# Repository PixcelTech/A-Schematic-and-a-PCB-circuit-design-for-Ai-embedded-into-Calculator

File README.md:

# A-Schematic-and-a-PCB-circuit-design-for-Ai-embedded-into-Calculator
A Schematic and a PCB circuit design for Ai embedded into Calculator

if you want it run it fine in your Kicad then download all the files in
the main branch and place them in a folder and then opened then opened that 
folder through Kicad.

CON 
it is a wifi connected and it has a small light then tell you if the wifi is working

light = blinking (wifi not working)

light = stable (wifi fine)

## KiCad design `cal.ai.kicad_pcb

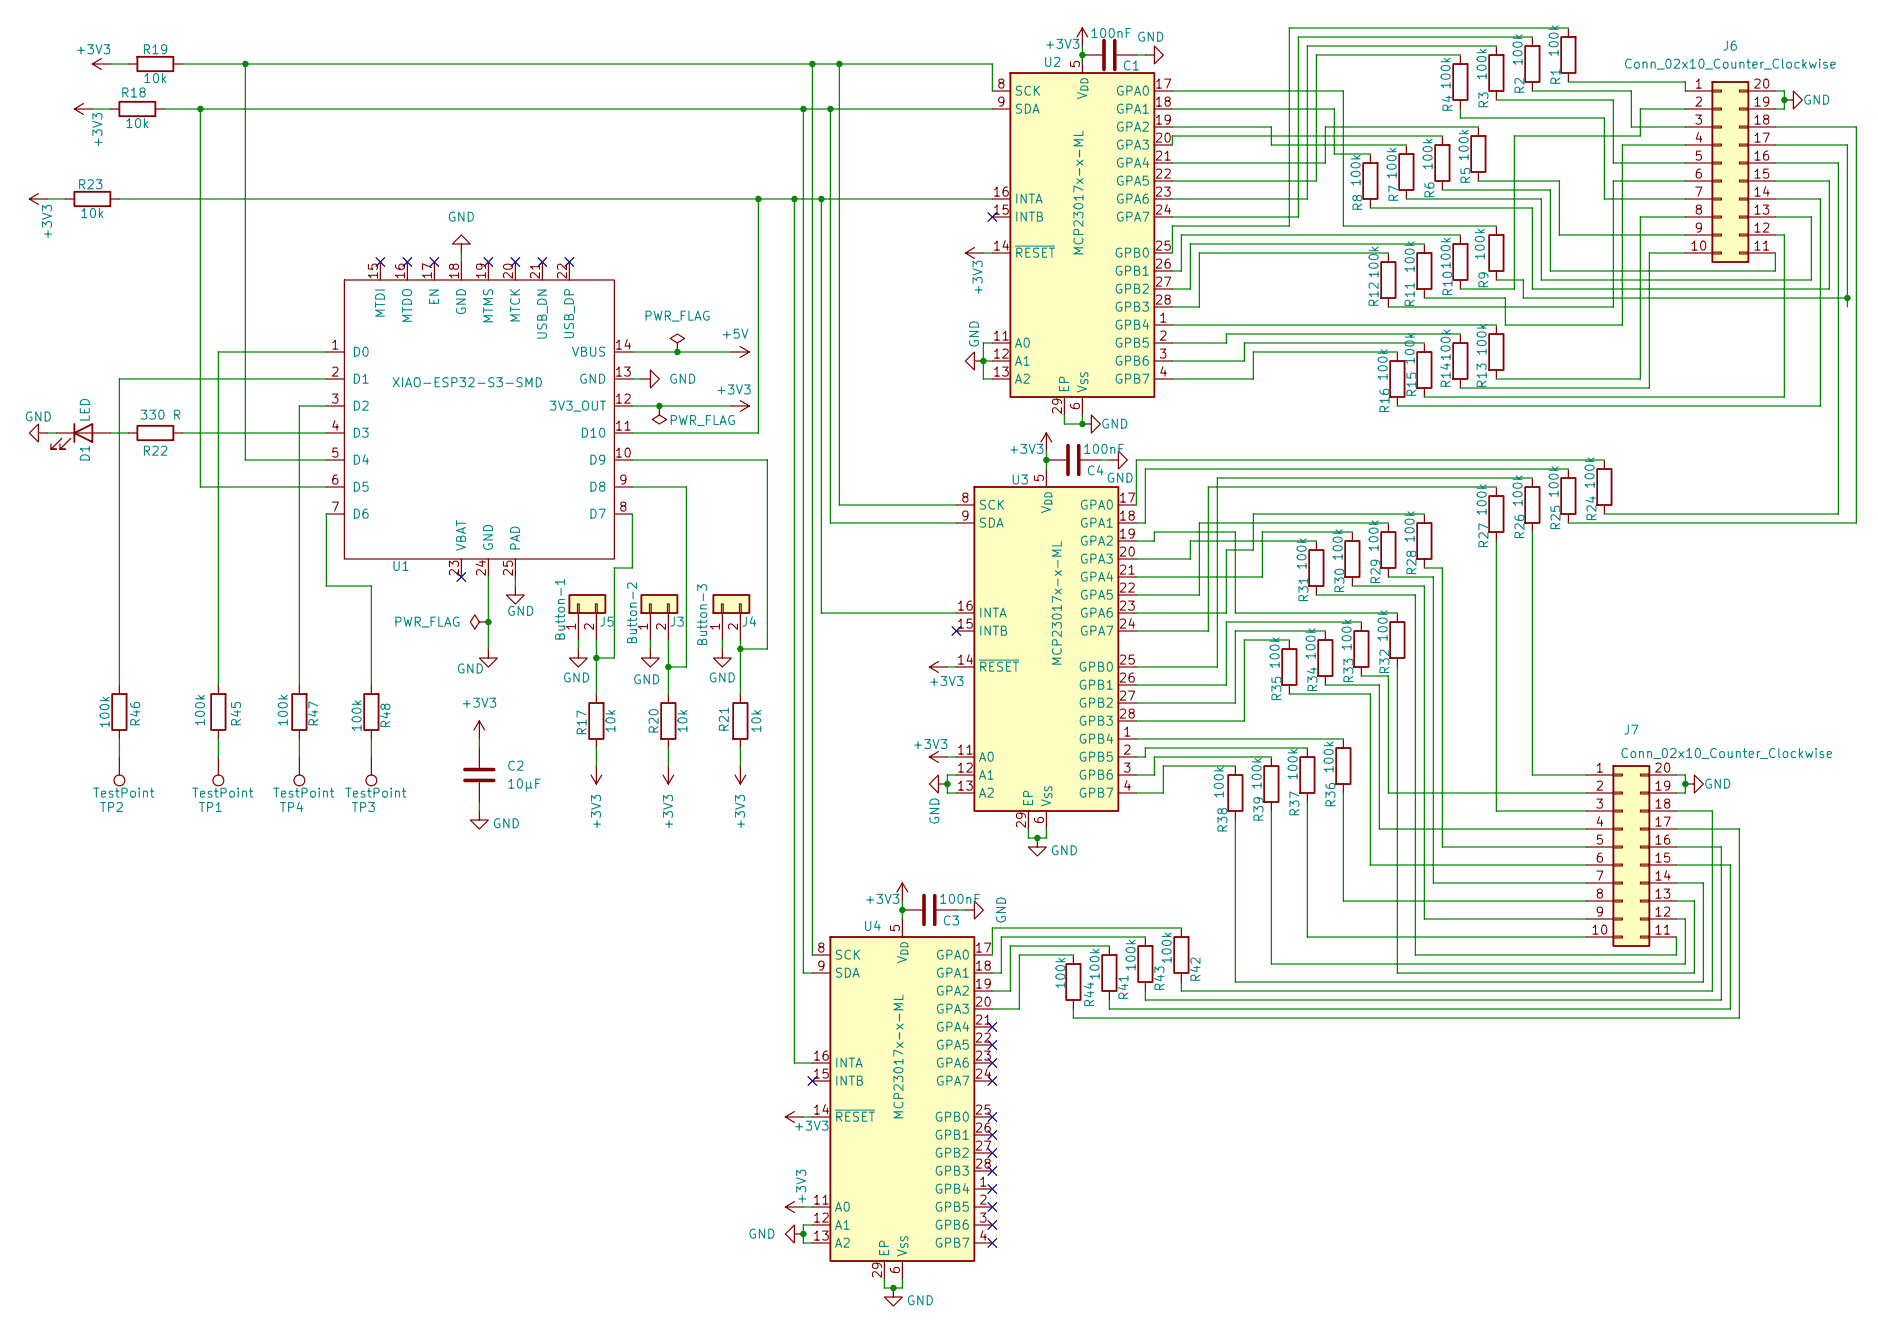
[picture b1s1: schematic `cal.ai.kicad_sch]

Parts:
C1, C3, C4: 100nF; C_0603_1608Metric
C2: 10µF; C_0805_2012Metric
D1: LED; LED_0402_1005Metric
J3: Button-2; PinHeader_1x02_P2.54mm_Vertical
J4: Button-3; PinHeader_1x02_P2.54mm_Vertical
J5: Button-1; PinHeader_1x02_P2.54mm_Vertical
J6, J7: Conn_02x10_Counter_Clockwise; PinHeader_2x10_P2.54mm_Vertical
R1, R2, R3, R4, R5, R6, R7, R8, R9, R10, R11, R12, R13, R14, R15, R16, R24, R25, R26, R27, R28, R29, R30, R31, R32, R33, R34, R35, R36, R37, R38, R39, R41, R42, R43, R44, R45, R46, R47, R48: 100k; R_0603_1608Metric
R17, R18, R19, R20, R21, R23: 10k; R_0603_1608Metric
R22: 330 R; R_0603_1608Metric
TP1, TP2, TP3, TP4: TestPoint; TestPoint_Loop_D1.80mm_Drill1.0mm_Beaded
U1: XIAO-ESP32-S3-SMD
U2, U3, U4: MCP23017x-x-ML; QFN-28-1EP_6x6mm_P0.65mm_EP4.25x4.25mm

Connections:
+3V3: C1.2, C2.1, C3.2, C4.2, R17.1, R18.1, R19.2, R20.2, R21.2, R23.1, U1.12 (3V3_OUT), U2.5 (V_{DD}), U2.14 (~RESET), U3.5 (V_{DD}), U3.11 (A0), U3.14 (~RESET), U4.5 (V_{DD}), U4.11 (A0), U4.14 (~RESET)
+5V: U1.14 (VBUS)
GND: C1.1, C2.2, C3.1, C4.1, D1.1 (K), J3.1, J4.1, J5.1, J6.19, J6.20, J7.19, J7.20, U1.13 (GND), U1.18 (GND), U1.24 (GND), U1.25 (PAD), U2.6 (V_{SS}), U2.11 (A0), U2.12 (A1), U2.13 (A2), U2.29 (EP), U3.6 (V_{SS}), U3.12 (A1), U3.13 (A2), U3.29 (EP), U4.6 (V_{SS}), U4.12 (A1), U4.13 (A2), U4.29 (EP)
unnamed: D1.2 (A), R22.1
unnamed: J3.2, R20.1, U1.9 (D8)
unnamed: J4.2, R21.1, U1.10 (D9)
unnamed: J5.2, R17.2, U1.8 (D7)
unnamed: J6.1, R1.1
unnamed: J6.2, R10.1
unnamed: J6.3, R2.1
unnamed: J6.4, R11.2
unnamed: J6.5, R3.1
unnamed: J6.6, R12.2
unnamed: J6.7, R4.1
unnamed: J6.8, R13.2
unnamed: J6.9, R5.1
unnamed: J6.10, R14.2
unnamed: J6.11, R6.1
unnamed: J6.12, R15.2
unnamed: J6.13, R7.1
unnamed: J6.14, R16.2
unnamed: J6.15, R8.1
unnamed: J6.16, R24.2
unnamed: J6.17, R9.1
unnamed: J6.18, R25.2
unnamed: J7.1, R26.2
unnamed: J7.2, R33.2
unnamed: J7.3, R27.2
unnamed: J7.4, R34.2
unnamed: J7.5, R28.2
unnamed: J7.6, R35.2
unnamed: J7.7, R29.2
unnamed: J7.8, R36.2
unnamed: J7.9, R30.2
unnamed: J7.10, R37.2
unnamed: J7.11, R31.2
unnamed: J7.12, R39.2
unnamed: J7.13, R32.2
unnamed: J7.14, R38.2
unnamed: J7.15, R41.1
unnamed: J7.16, R43.1
unnamed: J7.17, R44.1
unnamed: J7.18, R42.1
unnamed: R45.1, TP1.1 (1_1)
unnamed: R46.1, TP2.1 (1_1)
unnamed: R47.1, TP4.1 (1_1)
unnamed: R48.1, TP3.1 (1_1)
unnamed: R45.2, U1.1 (D0)
unnamed: R46.2, U1.2 (D1)
unnamed: R47.2, U1.3 (D2)
unnamed: R22.2, U1.4 (D3)
unnamed: R19.1, U1.5 (D4), U2.8 (SCK), U3.8 (SCK), U4.8 (SCK)
unnamed: R18.2, U1.6 (D5), U2.9 (SDA), U3.9 (SDA), U4.9 (SDA)
unnamed: R48.2, U1.7 (D6)
unnamed: R23.2, U1.11 (D10), U2.16 (INTA), U3.16 (INTA), U4.16 (INTA)
unnamed: R9.2, U2.17 (GPA0)
unnamed: R8.2, U2.18 (GPA1)
unnamed: R7.2, U2.19 (GPA2)
unnamed: R6.2, U2.20 (GPA3)
unnamed: R5.2, U2.21 (GPA4)
unnamed: R4.2, U2.22 (GPA5)
unnamed: R3.2, U2.23 (GPA6)
unnamed: R2.2, U2.24 (GPA7)
unnamed: R1.2, U2.25 (GPB0)
unnamed: R10.2, U2.26 (GPB1)
unnamed: R11.1, U2.27 (GPB2)
unnamed: R12.1, U2.28 (GPB3)
unnamed: R13.1, U2.1 (GPB4)
unnamed: R14.1, U2.2 (GPB5)
unnamed: R15.1, U2.3 (GPB6)
unnamed: R16.1, U2.4 (GPB7)
unnamed: R24.1, U3.17 (GPA0)
unnamed: R25.1, U3.18 (GPA1)
unnamed: R32.1, U3.19 (GPA2)
unnamed: R31.1, U3.20 (GPA3)
unnamed: R30.1, U3.21 (GPA4)
unnamed: R29.1, U3.22 (GPA5)
unnamed: R28.1, U3.23 (GPA6)
unnamed: R27.1, U3.24 (GPA7)
unnamed: R26.1, U3.25 (GPB0)
unnamed: R33.1, U3.26 (GPB1)
unnamed: R34.1, U3.27 (GPB2)
unnamed: R35.1, U3.28 (GPB3)
unnamed: R36.1, U3.1 (GPB4)
unnamed: R37.1, U3.2 (GPB5)
unnamed: R39.1, U3.3 (GPB6)
unnamed: R38.1, U3.4 (GPB7)
unnamed: R42.2, U4.17 (GPA0)
unnamed: R43.2, U4.18 (GPA1)
unnamed: R41.2, U4.19 (GPA2)
unnamed: R44.2, U4.20 (GPA3)

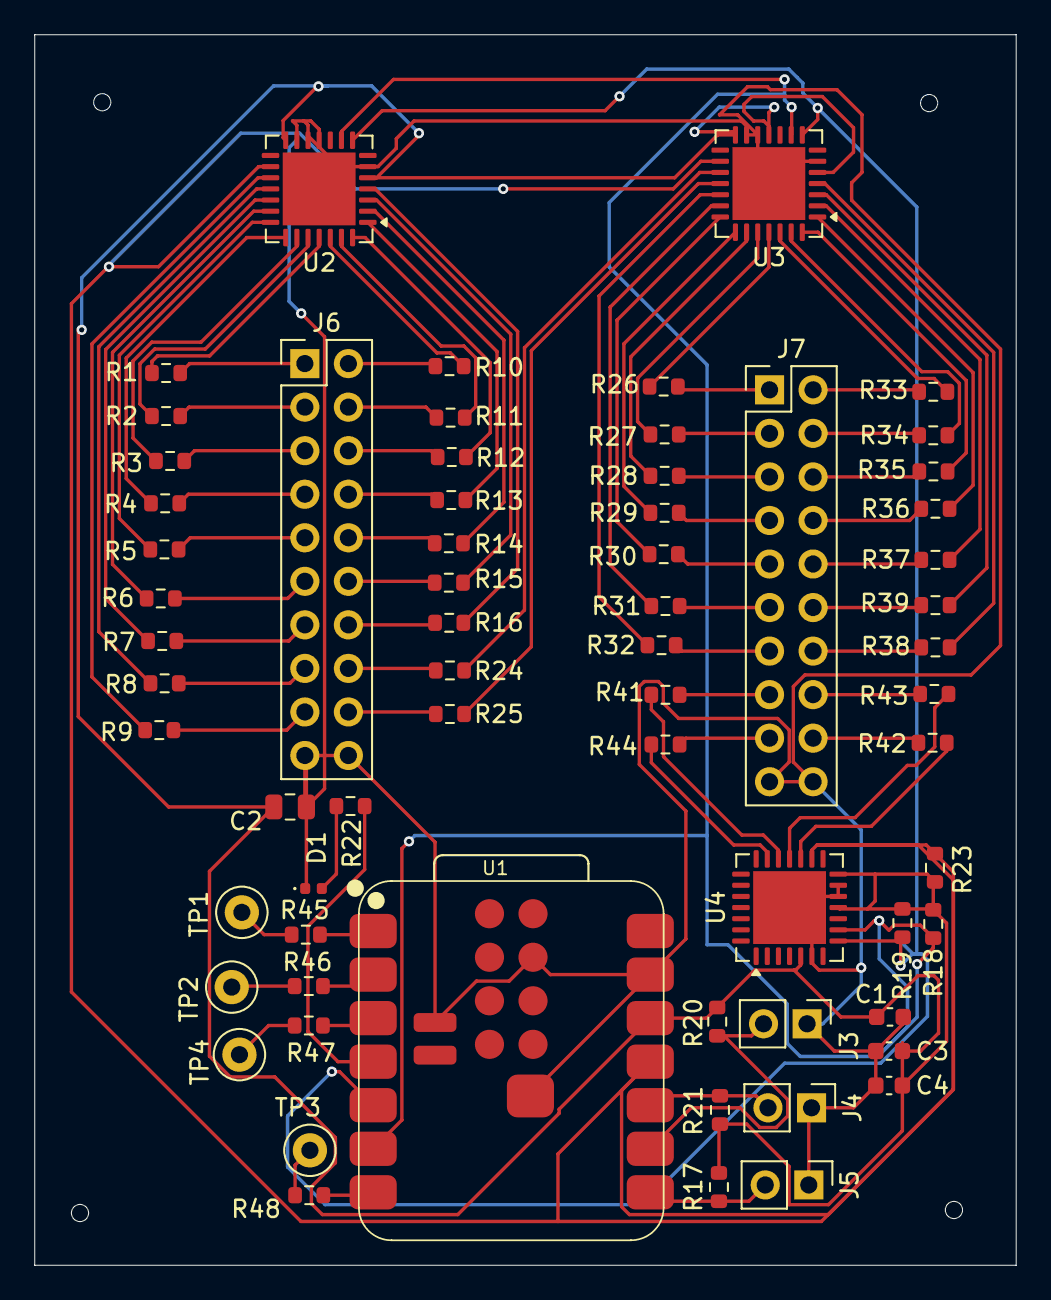
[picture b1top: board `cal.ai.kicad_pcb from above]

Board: 2 copper layers, 57.3 x 71.8 mm, 65 parts (0 on the bottom side), 90 nets.
